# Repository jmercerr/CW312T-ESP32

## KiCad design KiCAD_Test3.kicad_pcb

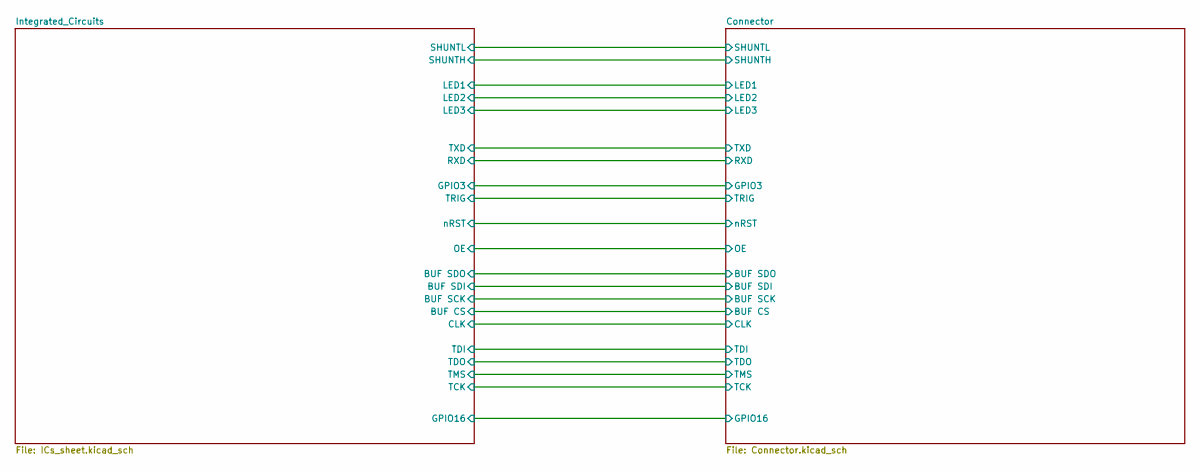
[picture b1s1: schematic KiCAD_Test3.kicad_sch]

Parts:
PCB1: CE; CE-Logo_8.5x6mm_SilkScreen
PCB2: Pb_Free; Pb_Free_8.0x8.0mm_SilkScreen
PCB3: WEEE; WEEE-Logo_8.4x12mm_SilkScreen

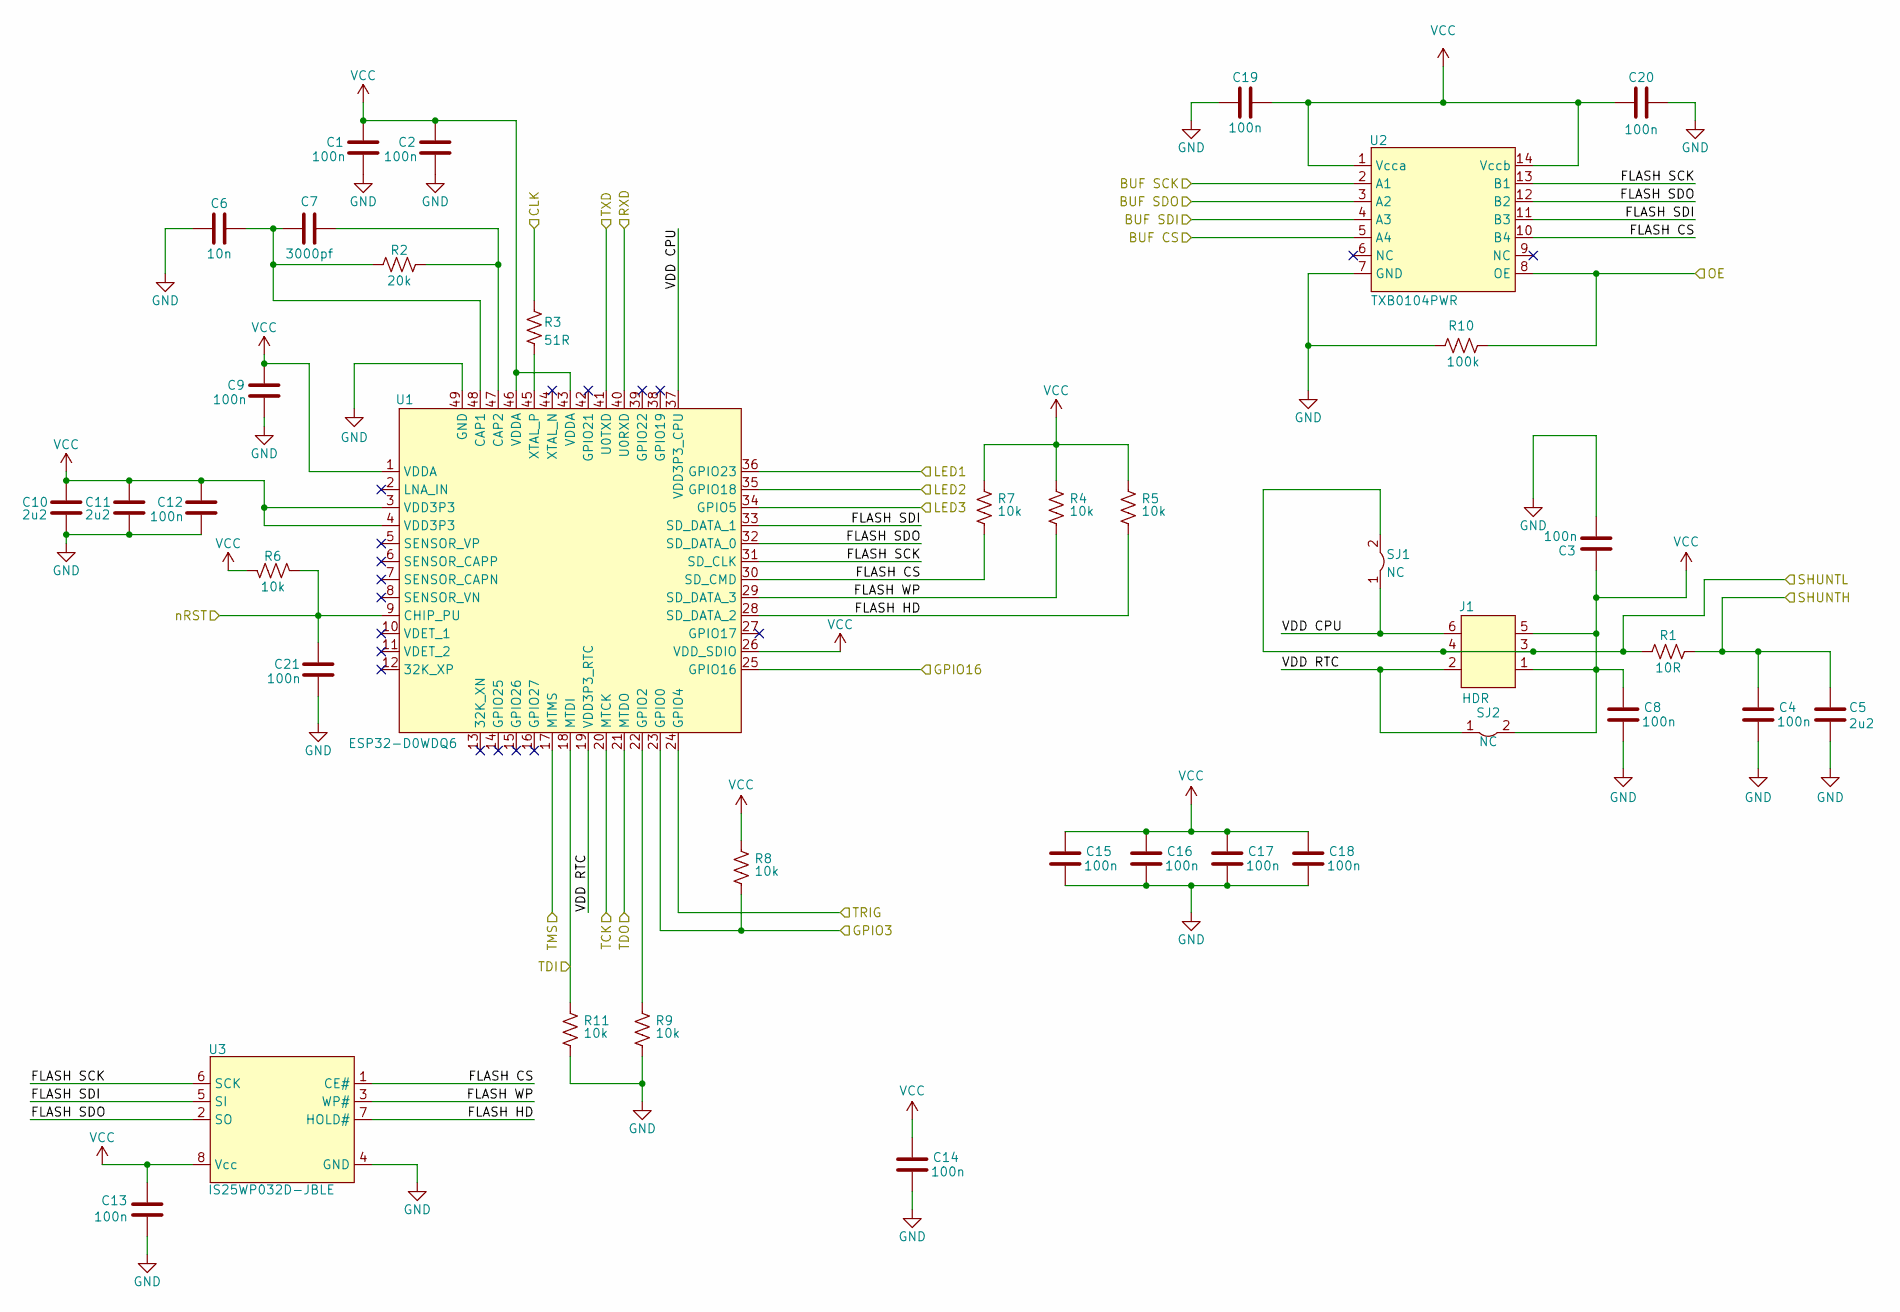
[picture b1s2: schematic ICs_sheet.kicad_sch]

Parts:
C1, C2, C3, C4, C8, C9, C12, C13, C14, C15, C16, C17, C18, C19, C20, C21: CAP_100n_6.3V_0603; C_0603_1608Metric; Manufacturer Part Number CC0603KRX7R5BB104
C5, C10, C11: CAP_2u2_6.3V_0603; C_0603_1608Metric; Manufacturer Part Number CC0603KRX7R5BB225
C6: CAP_10n_10V_0603; C_0603_1608Metric; Manufacturer Part Number CC0603KRX7R6BB103
C7: CAP_3000p_50V_0603; C_0603_1608Metric; Manufacturer Part Number CC0603JRNPO9BN302
J1: HDR_6_2.54; PinHeader_2x03_P1.00mm_Vertical; Manufacturer Part Number PH2-06-UA
R1: RES_10R_0603; R_0603_1608Metric; Manufacturer Part Number RC0603FR-0710RL
R2: RES_20k_0603; R_0603_1608Metric; Manufacturer Part Number RC0603FR-0720KL
R3: RES_51R_0603; R_0603_1608Metric; Manufacturer Part Number RC0603FR-0751RL
R4, R5, R6, R7, R8, R9, R11: RES_10k_0603; R_0603_1608Metric; Manufacturer Part Number RC0603FR-0710KL
R10: RES_100k_0603; R_0603_1608Metric; Manufacturer Part Number RC0603FR-07100KL
SJ1, SJ2: SolderJumper-2_P1.3mm_Bridged2Bar_Pad1.0x1.5mm
U1: ESP32-D0WDQ6; QFN-48-1EP_6x6mm_P0.4mm_EP4.3x4.3mm; Manufacturer Part Number ESP32-D0WDQ6
U2: TXB0104PWR; SOIC-14_3.9x8.7mm_P1.27mm; Manufacturer Part Number TXB0104PWR
U3: IS25WP032D; SOIC-8_5.275x5.275mm_P1.27mm; Manufacturer Part Number IS25WP032D-JBLE

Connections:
/Connector/BUF CS: U2.5 (A4); also elsewhere on the board
/Connector/BUF SCK: U2.2 (A1); also elsewhere on the board
/Connector/BUF SDI: U2.4 (A3); also elsewhere on the board
/Connector/BUF SDO: U2.3 (A2); also elsewhere on the board
/Connector/CLK: R3.2; also elsewhere on the board
/Connector/GPIO3: R8.1, U1.23 (GPIO0); also elsewhere on the board
/Connector/GPIO16: U1.25 (GPIO16); also elsewhere on the board
/Connector/LED1: U1.36 (GPIO23); also elsewhere on the board
/Connector/LED2: U1.35 (GPIO18); also elsewhere on the board
/Connector/LED3: U1.34 (GPIO5); also elsewhere on the board
/Connector/OE: R10.2, U2.8 (OE); also elsewhere on the board
/Connector/RXD: U1.40 (U0RXD); also elsewhere on the board
/Connector/SHUNTH: C4.1, C5.1, R1.2; also elsewhere on the board
/Connector/SHUNTL: J1.3, J1.4, R1.1, SJ1.2; also elsewhere on the board
/Connector/TCK: U1.20 (MTCK); also elsewhere on the board
/Connector/TDI: R11.2, U1.18 (MTDI); also elsewhere on the board
/Connector/TDO: U1.21 (MTDO); also elsewhere on the board
/Connector/TMS: U1.17 (MTMS); also elsewhere on the board
/Connector/TRIG: U1.24 (GPIO4); also elsewhere on the board
/Connector/TXD: U1.41 (U0TXD); also elsewhere on the board
/Connector/nRST: C21.1, R6.2, U1.9 (CHIP_PU); also elsewhere on the board
/Integrated_Circuits/FLASH CS: R7.1, U1.30 (SD_CMD), U2.10 (B4), U3.1 (CE#)
/Integrated_Circuits/FLASH HD: R5.1, U1.28 (SD_DATA_2), U3.7 (HOLD#)
/Integrated_Circuits/FLASH SCK: U1.31 (SD_CLK), U2.13 (B1), U3.6 (SCK)
/Integrated_Circuits/FLASH SDI: U1.33 (SD_DATA_1), U2.11 (B3), U3.5 (SI)
/Integrated_Circuits/FLASH SDO: U1.32 (SD_DATA_0), U2.12 (B2), U3.2 (SO)
/Integrated_Circuits/FLASH WP: R4.1, U1.29 (SD_DATA_3), U3.3 (WP#)
/Integrated_Circuits/VDD CPU: J1.6, SJ1.1, U1.37 (VDD3P3_CPU)
/Integrated_Circuits/VDD RTC: J1.2, SJ2.1, U1.19 (VDD3P3_RTC)
GND: C1.2, C2.2, C3.2, C4.2, C5.2, C6.1, C8.2, C9.2, C10.2, C11.2, C12.2, C13.2, C14.2, C15.2, C16.2, C17.2, C18.2, C19.2, C20.2, C21.2, R9.1, R10.1, R11.1, U1.49 (GND), U2.7 (GND), U3.4 (GND); also elsewhere on the board
unnamed: C6.2, C7.1, R2.1, U1.48 (CAP1)
unnamed: C7.2, R2.2, U1.47 (CAP2)
unnamed: R9.2, U1.22 (GPIO2)
unnamed: R3.1, U1.45 (XTAL_P)
VCC: C1.1, C2.1, C3.1, C8.1, C9.1, C10.1, C11.1, C12.1, C13.1, C14.1, C15.1, C16.1, C17.1, C18.1, C19.1, C20.1, J1.1, J1.5, R4.2, R5.2, R6.1, R7.2, R8.2, SJ2.2, U1.1 (VDDA), U1.3 (VDD3P3), U1.4 (VDD3P3), U1.26 (VDD_SDIO), U1.43 (VDDA), U1.46 (VDDA), U2.1 (Vcca), U2.14 (Vccb), U3.8 (Vcc); also elsewhere on the board

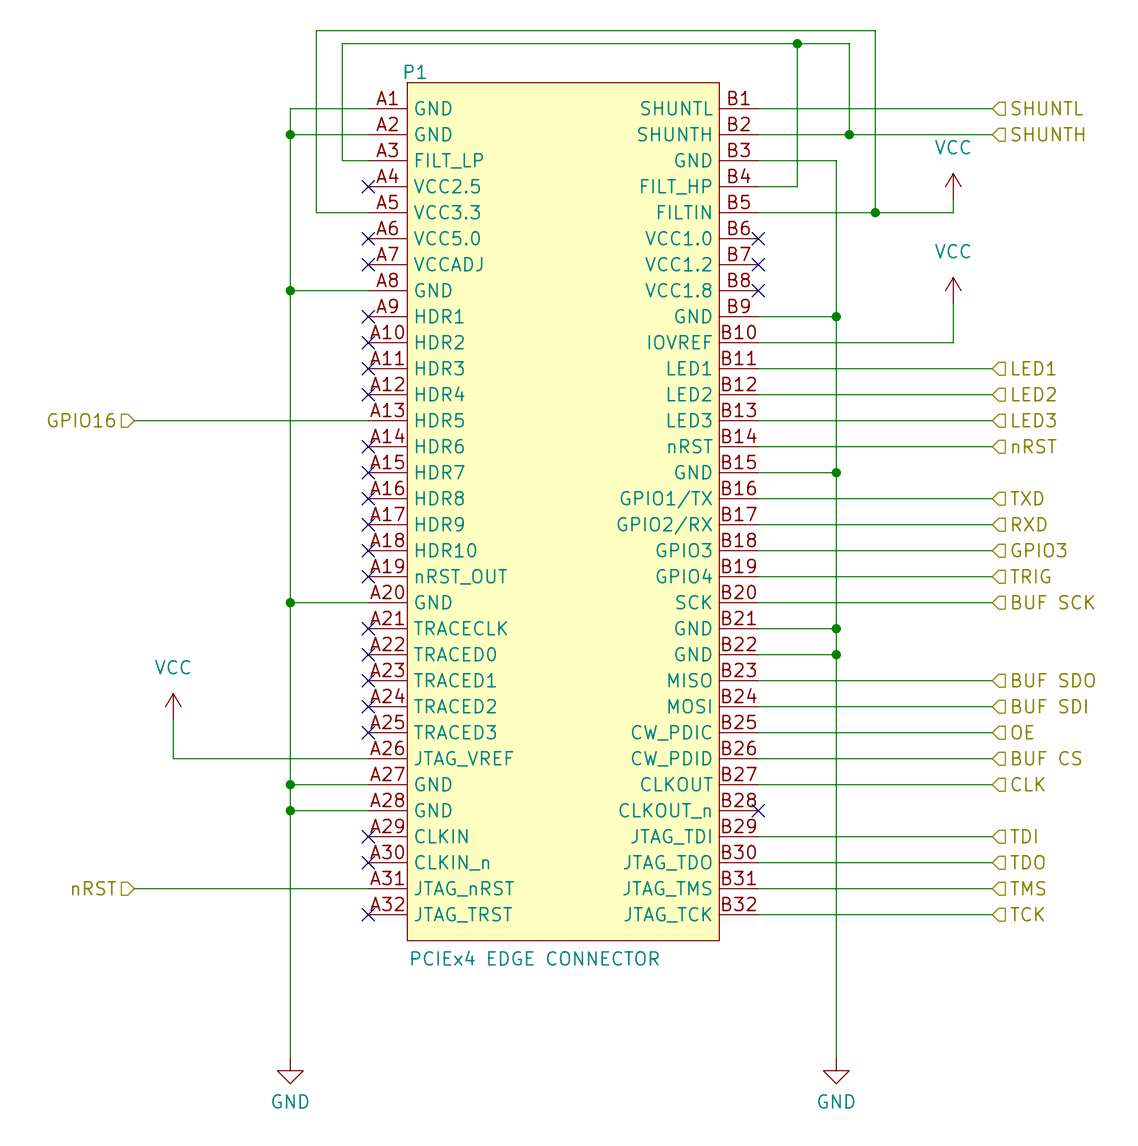
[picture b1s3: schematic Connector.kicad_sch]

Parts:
P1: PCIEx4 EDGE CONNECTOR; CW312_Template

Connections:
/Connector/BUF CS: P1.B26 (CW_PDID); also elsewhere on the board
/Connector/BUF SCK: P1.B20 (SCK); also elsewhere on the board
/Connector/BUF SDI: P1.B24 (MOSI); also elsewhere on the board
/Connector/BUF SDO: P1.B23 (MISO); also elsewhere on the board
/Connector/CLK: P1.B27 (CLKOUT); also elsewhere on the board
/Connector/GPIO3: P1.B18 (GPIO3); also elsewhere on the board
/Connector/GPIO16: P1.A13 (HDR5); also elsewhere on the board
/Connector/LED1: P1.B11 (LED1); also elsewhere on the board
/Connector/LED2: P1.B12 (LED2); also elsewhere on the board
/Connector/LED3: P1.B13 (LED3); also elsewhere on the board
/Connector/OE: P1.B25 (CW_PDIC); also elsewhere on the board
/Connector/RXD: P1.B17 (GPIO2/RX); also elsewhere on the board
/Connector/SHUNTH: P1.A3 (FILT_LP), P1.B2 (SHUNTH), P1.B4 (FILT_HP); also elsewhere on the board
/Connector/SHUNTL: P1.B1 (SHUNTL); also elsewhere on the board
/Connector/TCK: P1.B32 (JTAG_TCK); also elsewhere on the board
/Connector/TDI: P1.B29 (JTAG_TDI); also elsewhere on the board
/Connector/TDO: P1.B30 (JTAG_TDO); also elsewhere on the board
/Connector/TMS: P1.B31 (JTAG_TMS); also elsewhere on the board
/Connector/TRIG: P1.B19 (GPIO4); also elsewhere on the board
/Connector/TXD: P1.B16 (GPIO1/TX); also elsewhere on the board
/Connector/nRST: P1.A31 (JTAG_nRST), P1.B14 (nRST); also elsewhere on the board
GND: P1.A1 (GND), P1.A2 (GND), P1.A8 (GND), P1.A20 (GND), P1.A27 (GND), P1.A28 (GND), P1.B3 (GND), P1.B9 (GND), P1.B15 (GND), P1.B21 (GND), P1.B22 (GND); also elsewhere on the board
VCC: P1.A5 (VCC3.3), P1.A26 (JTAG_VREF), P1.B5 (FILTIN), P1.B10 (IOVREF); also elsewhere on the board

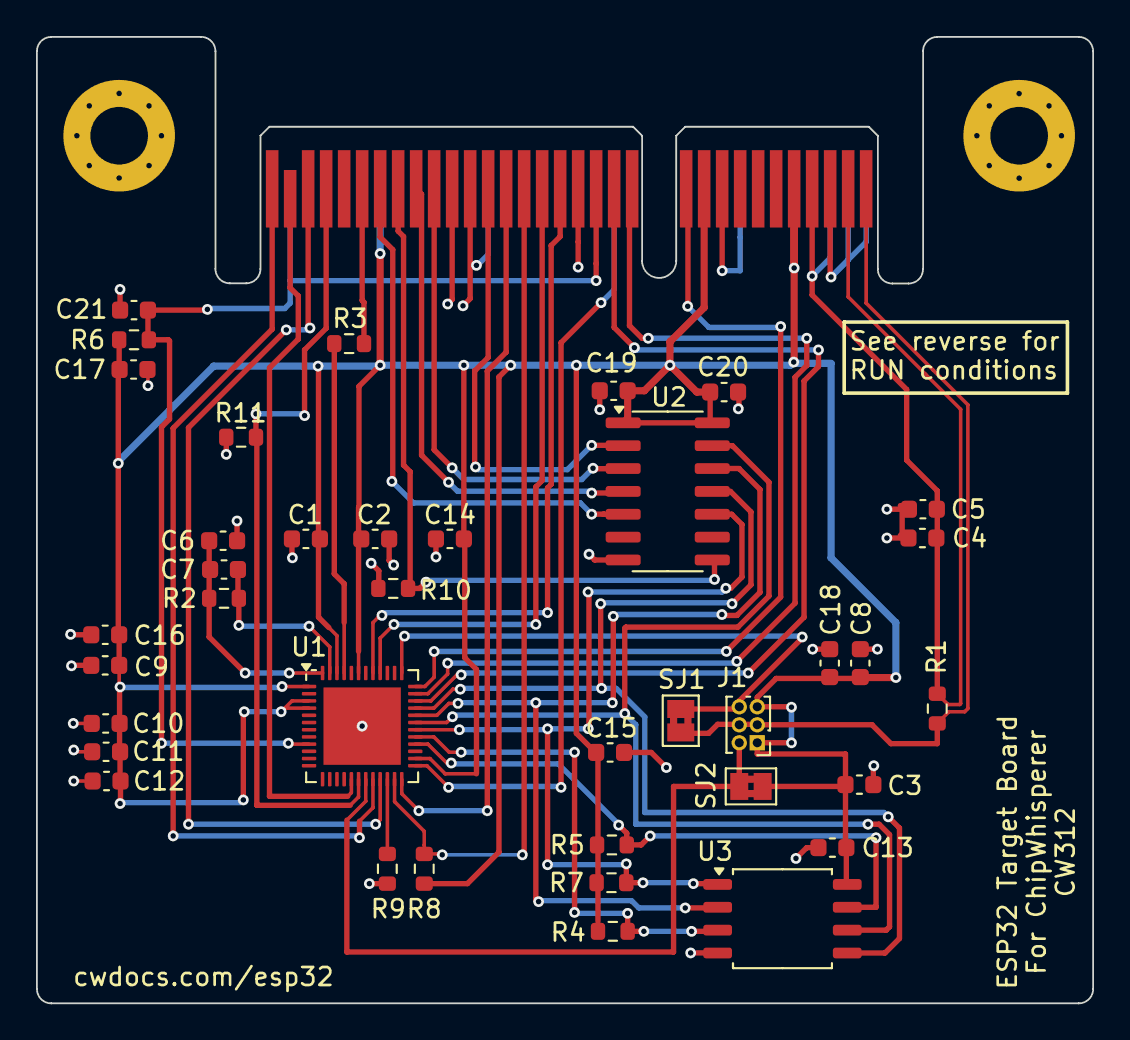
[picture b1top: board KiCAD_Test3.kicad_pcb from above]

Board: 2 copper layers, 58.7 x 53.7 mm, 43 parts (0 on the bottom side), 35 nets.

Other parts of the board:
PCB4: UKCA symbol; UKCA-Logo_8x8mm_SilkScreen
PCB5: CE Symbol; CE-Logo_8.5x6mm_SilkScreen
PCB6: WEEE SYMBOL; WEEE-Logo_5.6x8mm_SilkScreen
PCB7: Pb_Free Symbol; Pb_Free_8.0x8.0mm_SilkScreen

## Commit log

2024-11-08 initial commit of KiCAD files for ESP32 Target
2024-11-15 updated ESP32 design - needs silkscreen added and shunt should be moved to be closer to U1
2024-11-15 updated design for esp32
2024-11-21 updated design - removed visible pin numbers from passives, fixed connections, updated silkscreen
2024-11-22 updated cw312T template and production files
2024-12-19 updated pcb and schematic after library re-organization, also updated header to the correct footprint
